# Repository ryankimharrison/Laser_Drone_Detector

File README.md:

# Laser Turret

An experimental two-camera pan/tilt tracking platform that detects a handheld DGI drone, follows it with a differential stepper mechanism, and controls a low-power green laser through a deliberately fail-closed software interlock.

The narrow C270 has been replaced with an OV9281-class camera (exact USB module
still to be commissioned). See [CAMERA_UPGRADE.md](CAMERA_UPGRADE.md) for camera
profiles, required recalibration, the 5–10 m indoor flight dataset workflow, and
timing configuration. The replacement profile is tracking-only. Historical
measurements below describe the original rig unless explicitly stated otherwise.

This README explains both the big picture and the implementation. In plain language: a Windows computer watches two cameras, identifies the drone, estimates where it is moving, and asks a Raspberry Pi Pico to turn two motors. The laser is a separate output. Tracking the drone does **not** automatically permit the laser to turn on; a set of additional checks must all pass on every control cycle.

## What is in this repository?

| Area | Purpose |
|---|---|
| `turret_host/` | Windows/Python application: cameras, object and face detection, tracking, motion control, GUI, calibration, logging, and serial communication |
| `firmware/current/` | Current MicroPython firmware for the Raspberry Pi Pico |
| `turret-2026-03-27_134819/` | KiCad schematic and PCB layout for controller board revision `3/27/2026 prod v1` |
| `tools/` | Calibration, deployment, diagnostics, replay, registration, and analysis utilities |
| `tests/` | Host-side regression tests, principally for telemetry and microstepping |
| `dataset/`, `models/`, `weights/` | Local training data and detector artifacts; most generated content is intentionally ignored by Git |
| `firmware/backups/` | Historical, timestamped firmware snapshots; useful for archaeology, not the current implementation |
| `staged/` | Proposed patches and experiments that may not be active |

The authoritative implementation paths are `turret_host/`, `firmware/current/`, and the KiCad project. Documents such as `AGENT_HANDOFF.md`, `DETECTION_BRIEF.md`, session notes, and staged patches preserve valuable history, but some statements in them have since been superseded by measurements or code changes.

## System overview

The physical head carries a narrow camera, a wide camera, a laser, and an inertial measurement unit (IMU). Two stepper motors drive a differential wrist. The computer performs the expensive vision and tracking work; the Pico generates accurate step pulses, applies motion limits, operates switched outputs, and stops motion if host commands disappear.

```mermaid
flowchart LR
    W[Wide camera<br/>find and reacquire] --> DW[Wide detector]
    N[Narrow camera<br/>precision tracking] --> DN[Drone detector]
    N --> F[YuNet face detector]
    DW --> X[Wide-to-narrow mapping]
    DN --> T[Pixel tracker]
    X --> T
    T --> C[Controller]
    F --> I[Laser interlock]
    C --> I
    I --> L[Serial link]
    L --> P[Raspberry Pi Pico]
    P --> M[Two stepper drivers]
    P --> Q[Laser MOSFET]
    IMU[Payload IMU] --> P
    P --> L
```

The design separates responsibilities:

- The **host computer** understands images, chooses a target, predicts motion, calculates motor rates, presents status, and decides whether the laser is permitted.
- The **Pico firmware** performs deterministic pulse generation, differential kinematics, acceleration limiting, travel guarding, output control, and a 400 ms command watchdog.
- The **PCB** connects power, the Pico, plug-in stepper drivers, motor and sensor headers, and three MOSFET-switched loads.

## How one frame becomes motion

1. Dedicated capture threads continuously grab the newest narrow and wide camera frames.
2. YOLO detects candidate drones. Wide-camera detections can help find a target outside the narrow field of view.
3. A stateful pixel tracker associates detections across frames and estimates position and velocity.
4. The controller compares the predicted target position with the calibrated laser aim point.
5. A measured image Jacobian converts the required image motion into signed rates for the two motors.
6. The host sends `vel <motor-a> <motor-b>` commands over USB serial.
7. The Pico ramps toward those rates and generates step pulses using RP2040 PIO hardware.
8. If new commands stop arriving for 400 ms, the firmware ramps the motors to zero and cuts the laser.

Instead of queues, threads exchange data through a `Slot`: a one-item, newest-wins mailbox. This is important for real-time behavior. If vision falls behind, processing an old queue of frames would make the turret chase where the target *was*. A slot lets a slow consumer skip frames and act on the freshest available observation.

## Computer vision and target tracking

### Two cameras, two roles

The **wide camera** provides situational awareness and reacquisition. It is an SVPRO USBFHD01M/OV2710 module with an approximately 108° horizontal field of view. It normally runs at 1920×1080 at 30 fps, with an optional 1280×720 at 60 fps mode.

The **narrow camera** provides the precision image coordinate system. Its replacement profile is provisionally 1280×800 at 30 fps, monochrome and global shutter; USB identity, lens, mode, exposure and mounting must be commissioned. The previous C270 ran at 1280×720 at 30 fps, mounted 90° clockwise with its IR-cut filter removed, and remains available as an explicit comparison profile. Camera-dependent calibration is checked against the selected camera, lens, size and mount.

The wide-to-narrow transformation can steer the turret toward a target seen only by the wide camera. It includes camera rotation, focal-length scaling, and optional fitted registration. However, parallax and calibration error mean a wide-origin box is never considered precise enough to authorize the laser. The design rule is:

> **Track on either camera; fire only from current narrow-camera evidence.**

### Drone detection

`turret_host/detector.py` wraps an Ultralytics YOLO detector. The active default is the project-specific `drone_y11n_v4_1280.pt`, run at 1280-pixel input size with FP16 enabled where supported. Only the `drone` class is selected.

The detector proposes boxes; it does not by itself decide which box to follow or whether the laser may operate. Training and capture utilities support collecting in-domain images, pre-labeling them, reviewing labels, and training a small model. This matters because the real scene—a close drone held in a hand, indoors, with partial occlusion and altered camera color response—is unlike the small outdoor drones found in most public datasets.

### Association and prediction

`turret_host/tracker.py` implements a pixel-space Kalman tracker with state:

```text
[horizontal position, vertical position, horizontal velocity, vertical velocity]
```

It uses confidence, spatial gating, box geometry, and continuity to associate detections. Adaptive process noise lets it remain smooth during steady motion while responding more quickly when the target changes direction. Its state machine is:

- `SEARCH`: no reliable target.
- `ACQUIRE`: a candidate is being confirmed.
- `TRACK`: the detector and filter agree on a target.
- `COAST`: detections were briefly lost, so the filter is predicting without fresh pixel evidence.

Coasting is useful for smooth pointing but is **not** sufficient permission to fire. The interlock requires a fresh narrow-camera drone box, not just a plausible prediction.

Range is estimated from apparent drone size when possible and may be supplemented by camera geometry. The assumed physical drone width is part of the configuration, so this is an estimate rather than a depth sensor measurement.

### Motion compensation and control

The controller combines two ideas:

- **Proportional correction** moves the target toward the goal pixel.
- **Feedforward** uses estimated target velocity so the turret moves with the target instead of always lagging behind it.

The core control law is conceptually:

```text
motor rate = - inverse(image Jacobian) × (position correction + target image velocity)
```

The image Jacobian is measured during calibration by moving the mechanism and observing how a stationary scene shifts in the camera. Its sign and scale are machine-specific. Rates are clamped, derated near travel limits, and converted through the differential mechanism. Optical flow and IMU-derived platform motion can improve the velocity estimate; their quality gates and fallbacks are logged so recorded runs can be analyzed rather than tuned by impression.

## How face protection works

The active face detector is OpenCV YuNet. It runs in a dedicated thread on the **narrow camera** because CPU inference can take longer than one camera frame period. YuNet expects upright faces, so the narrow image is rotated to compensate for the camera's 90° physical mounting. Detected boxes are then mapped back to the raw narrow-camera coordinate system used by tracking and control.

The interlock measures the distance between every detected face box and the intended beam path. The path is treated as a segment between the calibrated laser goal and current target location rather than as a single point. If a face is within the configured 120-pixel exclusion margin, the laser is inhibited.

Just as importantly, a missing or old face report is treated as **unknown**, not “no face.” A stalled detector, dead camera thread, clock error, or face result older than 200 ms therefore turns the laser off.

### The laser permission checklist

`LaserInterlock` grants permission only when **all** of the following are true:

| Check | Meaning |
|---|---|
| Armed | Both configuration and the operator's deliberate arm action allow laser use |
| Tracking | The tracker is in confirmed `TRACK`, not searching, acquiring, or coasting |
| Goal calibrated | The image location where the beam lands has been physically measured |
| Fresh drone lock | A recent narrow-camera drone box exists and contains the entire beam path |
| Plausible shape | The box aspect ratio is consistent with the measured drone, rejecting a known hand-like false positive |
| Fresh face report | The face detector has reported recently enough to be trusted |
| Face clear | Every face is farther than the inhibit margin from the beam path |
| Settled | The platform angular rate is below the firing threshold |
| Aim error small | The tracked target is close enough to the calibrated beam point |
| Velocity stream fresh | A motion command was successfully sent within the last 100 ms |
| Duty limit | Continuous on-time has not exceeded the configured cap; a cooldown follows a trip |

The logic is permission-based: a current drone detection under the beam is positive evidence. Merely failing to see a face is never enough. On any failed check, the desired laser state changes to off before normal motion work continues.

Additional protections include:

- Operator stop, disarm, E-stop, shutdown, and dead-worker events set a host-side **latched safety veto**. It can only be cleared by a new human arm action.
- Arming on real hardware invokes a live face-interlock verification procedure.
- A refused firmware `laser on` is not retried forever.
- The serial writer prioritizes laser state transitions and reports when a dead link makes software unable to confirm that the beam is off.
- Firmware boot and exception paths park STEP/DIR and all MOSFET gates low.
- The velocity watchdog cuts the laser as well as stopping motion.

### What this protection cannot guarantee

The software currently detects **visible faces**, not all human heads. YuNet can miss profiles, the back of a head, heavy occlusion, poor lighting, motion blur, or a strongly tilted face. The repository records a known loss around 35° of in-plane head tilt in one test configuration. The 200 ms allowable report age also permits real-world motion within the safety margin.

Only narrow-camera faces participate in the firing veto. Wide-camera face boxes are drawn for awareness but are not geometrically calibrated into the beam coordinate system and do not gate the laser.

No software command can switch off a laser after power or serial control has failed in a state that leaves the output energized. A physical, normally-off power interlock, keyed enable, emergency stop that removes laser power, enclosure/beam stop, and appropriate protective eyewear are outside this repository and remain necessary. Cheap 532 nm DPSS modules may also emit invisible infrared unless properly filtered.

## Firmware architecture

The firmware runs on a Raspberry Pi Pico/RP2040 under MicroPython.

| Module | Responsibility |
|---|---|
| `main.py` | Safe boot, pin parking, and console startup |
| `cli.py` | USB serial command protocol and operational workflows |
| `stepper.py` | PIO step generation, position moves, velocity loop, acceleration, watchdog, and optional microstep profiles |
| `kinematics.py` | Differential transform between motor motion and payload pitch/yaw |
| `guard.py` | IMU-backed crash/travel protection |
| `imu.py` | GY-85 gyro, accelerometer, and magnetometer drivers |
| `datum.py` | Gravity/yaw datum handling |
| `endstop.py` | Endstop debouncing, homing, and repeatability tests |
| `peripherals.py` | Laser, IR light, fan, ultrasonic, analog, and I²C devices with safety checks |
| `pinmap.py` | Copper-verified board wiring; the hardware source of truth |
| `config.py` | Driver type, mechanics, limits, interlocks, and timing |
| `diagnostics.py` | Electrical and motion self-tests |

The differential wrist is not a conventional independent pan motor plus tilt motor. Both motors moving in the same direction produce pitch; moving oppositely produces yaw. Each motor by itself produces a mixture. `kinematics.py` performs this transform using the 26-tooth motor and 60-tooth miter pulley ratio.

Position moves and continuous velocity mode use RP2040 PIO state machines for deterministic pulses. A 5 ms firmware velocity tick ramps rates and enforces limits. Dynamic microstepping exists but is disabled by default because measured switching disturbances outweighed its benefit on this drivetrain.

## PCB and hardware design

The KiCad design is a single controller/carrier board centered on:

- **A1 — Raspberry Pi Pico:** USB-connected control computer and I/O controller.
- **A2/A3 — Pololu-format stepper sockets:** intended symbol is DRV8825, while the installed/configured drivers are A4988-compatible modules.
- **U1 — XL1509-5.0 buck regulator:** creates the board's 5 V rail from the external motor supply, with L1, D1, and bulk capacitors.
- **Q1/Q2/Q4 — low-side N-channel MOSFET outputs:** switch the laser, IR illuminator, and fan.
- **J2/J3:** four-wire motor coil connectors.
- **J13/J14:** endstop connectors.
- **J5/J11:** sensor/I²C connections; the GY-85 is configured on J5/I²C0.
- **J10/J9/J7:** laser, IR, and fan switched-load connectors.

The Pico is USB-powered; the PCB's 5 V rail does not feed Pico `VSYS`. Grounds are common. This means the controller does not operate as a standalone board without USB power.

### GPIO summary

| Function | GPIO |
|---|---:|
| Tilt motor DIR / STEP | 0 / 1 |
| Tilt microstep M2/M1/M0 / enable | 2 / 3 / 4 / 5 |
| Tilt driver pad 2 | 6 |
| Pan motor DIR / STEP | 7 / 8 |
| Pan microstep M2/M1/M0 / enable | 9 / 10 / 11 / 12 |
| Pan driver pad 2 | 13 |
| IR / fan / endstop 1 / laser | 14 / 15 / 16 / 17 |
| Endstop 2 | 19 |
| J5 I²C0 SDA/SCL | 20 / 21 |
| J11 I²C1 SDA/SCL | 26 / 27 |
| Analog input | 28 / ADC2 |

### Important PCB findings and rework

These are facts encoded in `firmware/current/pinmap.py` and `config.py`, not generic warnings:

1. **Tilt STEP and DIR net labels are swapped in the schematic.** The copper is usable; firmware follows the physically verified GPIO0=DIR and GPIO1=STEP mapping.
2. **Driver socket pad 2 differs between DRV8825 and A4988.** It is `FAULT` on a DRV8825 but logic `VDD` on an A4988. The current configuration drives it from a Pico GPIO as an acknowledged, marginal workaround; the documented preferred rework is a proper 3.3 V connection.
3. **RESET/SLEEP is reportedly tied to 5 V.** This violates the A4988 input limit when its logic supply is 3.3 V and is explicitly recorded as an accepted out-of-spec condition, not a safe design recommendation.
4. **Several sensor connectors expose 5 V next to direct RP2040 inputs.** The ultrasonic echo, analog sensor return, and powered endstop arrangements have no divider or clamp. RP2040 GPIO is not 5 V tolerant; only dry-contact-to-ground endstops or verified 3.3 V signals are safe.
5. **The motor connectors are mirrored.** Each keeps a coil on adjacent pins, but supplied interleaved looms must be re-pinned so each coil occupies pins 1–2 or 3–4. Incorrect wiring can make a motor buzz and overheat its driver.
6. **The TO-220 MOSFET footprint pin order did not match a standard device.** Q1/Q2/Q4 require crossed gate/drain leads or a matching pinout. Current config says this rework was completed; verify the physical board.
7. **There are no on-board I²C pull-ups.** Any attached module must provide correctly referenced 3.3 V pull-ups.

For any new revision, these should be corrected in copper instead of perpetuated as assembly workarounds.

## Homing, calibration, and coordinate systems

The turret has multiple coordinate systems: wide pixels, raw narrow pixels, upright display pixels, motor microsteps, payload pitch/yaw, and the real laser spot. Calibration is what connects them.

At startup, the normal application establishes a repeatable datum by checking the link, calibrating gyro bias, leveling from gravity, finding a yaw reference, applying a consistent backlash preload, and setting home. Pitch is observable from gravity. Yaw is not; the project uses the repeatable magnetic field of the nearby motors as a local datum rather than trusting it as a compass.

Required calibration artifacts include:

- **Image Jacobian:** how motor steps move a stationary feature in the narrow image.
- **Goal pixel:** where the real laser spot lands in the narrow image. Frame center is acceptable for aiming experiments but never for firing permission.
- **Wide-to-narrow registration:** how a wide detection maps into the narrow camera for reacquisition.
- **Camera/latency measurements:** focal geometry, exposure, frame delivery, and end-to-end delay.

Mechanical backlash was measured around 0.57°, so homing approaches the final datum from a consistent direction.

## Running the software

The recorded development environment is Windows with Python 3.12, OpenCV, NumPy, Pillow, pyserial, PyTorch with CUDA, and Ultralytics. A `.venv` directory exists in this checkout, but virtual environments are machine-specific and its Python launcher may point to an interpreter that is no longer installed. The repository currently has no reproducible lock file; treat the environment description as informative rather than a clean-install guarantee, and rebuild the environment locally when necessary.

Start safely with simulation and no GUI:

```powershell
.\.venv\Scripts\python.exe -m turret_host.app --no-hardware --no-gui --run-seconds 5
```

Run simulation with the spectator GUI:

```powershell
.\.venv\Scripts\python.exe -m turret_host.app --no-hardware
```

Run with real cameras and motion but force tracking-only behavior:

```powershell
.\.venv\Scripts\python.exe -m turret_host.app --tracking-only
```

The real-hardware default performs homing and may move the mechanism. Keep the laser power physically disconnected during commissioning. Useful options include `--port`, `--cpu`, `--wide-fast`, `--fast-home`, `--skip-level`, `--record DIR`, and `--run-seconds N`; use `--help` for the current list.

## Verification and diagnostics

Tests that do not require attached hardware:

```powershell
.\.venv\Scripts\python.exe -m compileall -q turret_host
.\.venv\Scripts\python.exe -m unittest discover -s tests
.\.venv\Scripts\python.exe -m turret_host.control
.\.venv\Scripts\python.exe -m turret_host.tracker
```

Many utilities in `tools/` intentionally talk to real hardware or cameras. Read their arguments and source before running them. In particular, deployment, homing, calibration, step, lash, and structured-light tools can cause motion or light emission.

The application can record synchronized telemetry for after-action analysis. The supporting scripts study latency, clock alignment, step integrity, image registration, optical-flow velocity, aim residuals, and mechanical skew. This measurement-first approach is central to the project: motor counts alone cannot reveal a skipped belt or stalled mechanism, and a visually smooth demo does not prove that the safety gates worked.

## Known limitations and current status

- This working tree is an active prototype with uncommitted current-code changes and staged experiments.
- Laser enable is currently `True` in both `turret_host/config.py` and `firmware/current/config.py`. The GUI still requires deliberate arming and the interlock still applies, but configuration is not a physical safety barrier.
- Face detection is a safety aid with known blind spots, not proof that no head is present.
- Wide-camera detections can steer but cannot authorize firing.
- Several camera intrinsics and offsets began as estimates; verify which calibration JSON artifacts exist on the actual machine.
- Dead reckoning can diverge when motors skip. The payload accelerometer independently measures tilt, but it cannot directly observe yaw near level.
- The software soft limits do not replace mechanical stops. The payload is documented as ±90° pitch with a ±225° yaw wiring limit.
- The host presently caps normal motor commands at 1000 microsteps/s pending further delivery testing, below firmware's higher electrical ceiling.
- Hardware notes describe accepted out-of-spec wiring. A production revision should add real level shifting/protection and a hardware laser-interlock chain.

## Design principles worth preserving

- **Fail closed:** uncertainty removes permission; it never creates it.
- **Freshness is data:** every frame, face report, detection, and command carries time information.
- **Newest wins:** discard stale work instead of building a real-time backlog.
- **Measure geometry:** do not hide sign errors or physical offsets in tuning constants.
- **Separate tracking from firing:** a prediction may steer, but only current narrow-camera evidence can permit light.
- **Independent witnesses:** use camera evidence, serial freshness, IMU attitude, firmware watchdogs, and human controls for different failure modes.
- **Preserve provenance:** a mapped wide-camera box remembers that it came from the wide camera and can never accidentally become firing evidence.

## Further reading

- `turret_host/BUILD_SPEC.md` — host design contract and hard-won implementation constraints.
- `turret_host/STATUS.md` — an older formal safety review; useful history, but some configuration values are now outdated.
- `AGENT_HANDOFF.md` — detailed hardware measurements, firmware protocol, and project history.
- `DETECTION_BRIEF.md` — rationale for the custom drone dataset and detector training approach.
- `PLAN_NEXT_STAGE.md` and session notes — experimental results and next-stage control analysis.
- `firmware/current/pinmap.py` — the copper-verified wiring source of truth.

## Responsible use

This project combines automated aiming, moving machinery, exposed electronics, and laser emission. Operate it only in a controlled indoor test area with a beam stop, exclusion zone, direct supervision, and a physical means to remove laser power. Begin with the laser disconnected and substitute a harmless indicator during software development. Compliance with local laser, electrical, workplace, and aviation rules is the operator's responsibility.

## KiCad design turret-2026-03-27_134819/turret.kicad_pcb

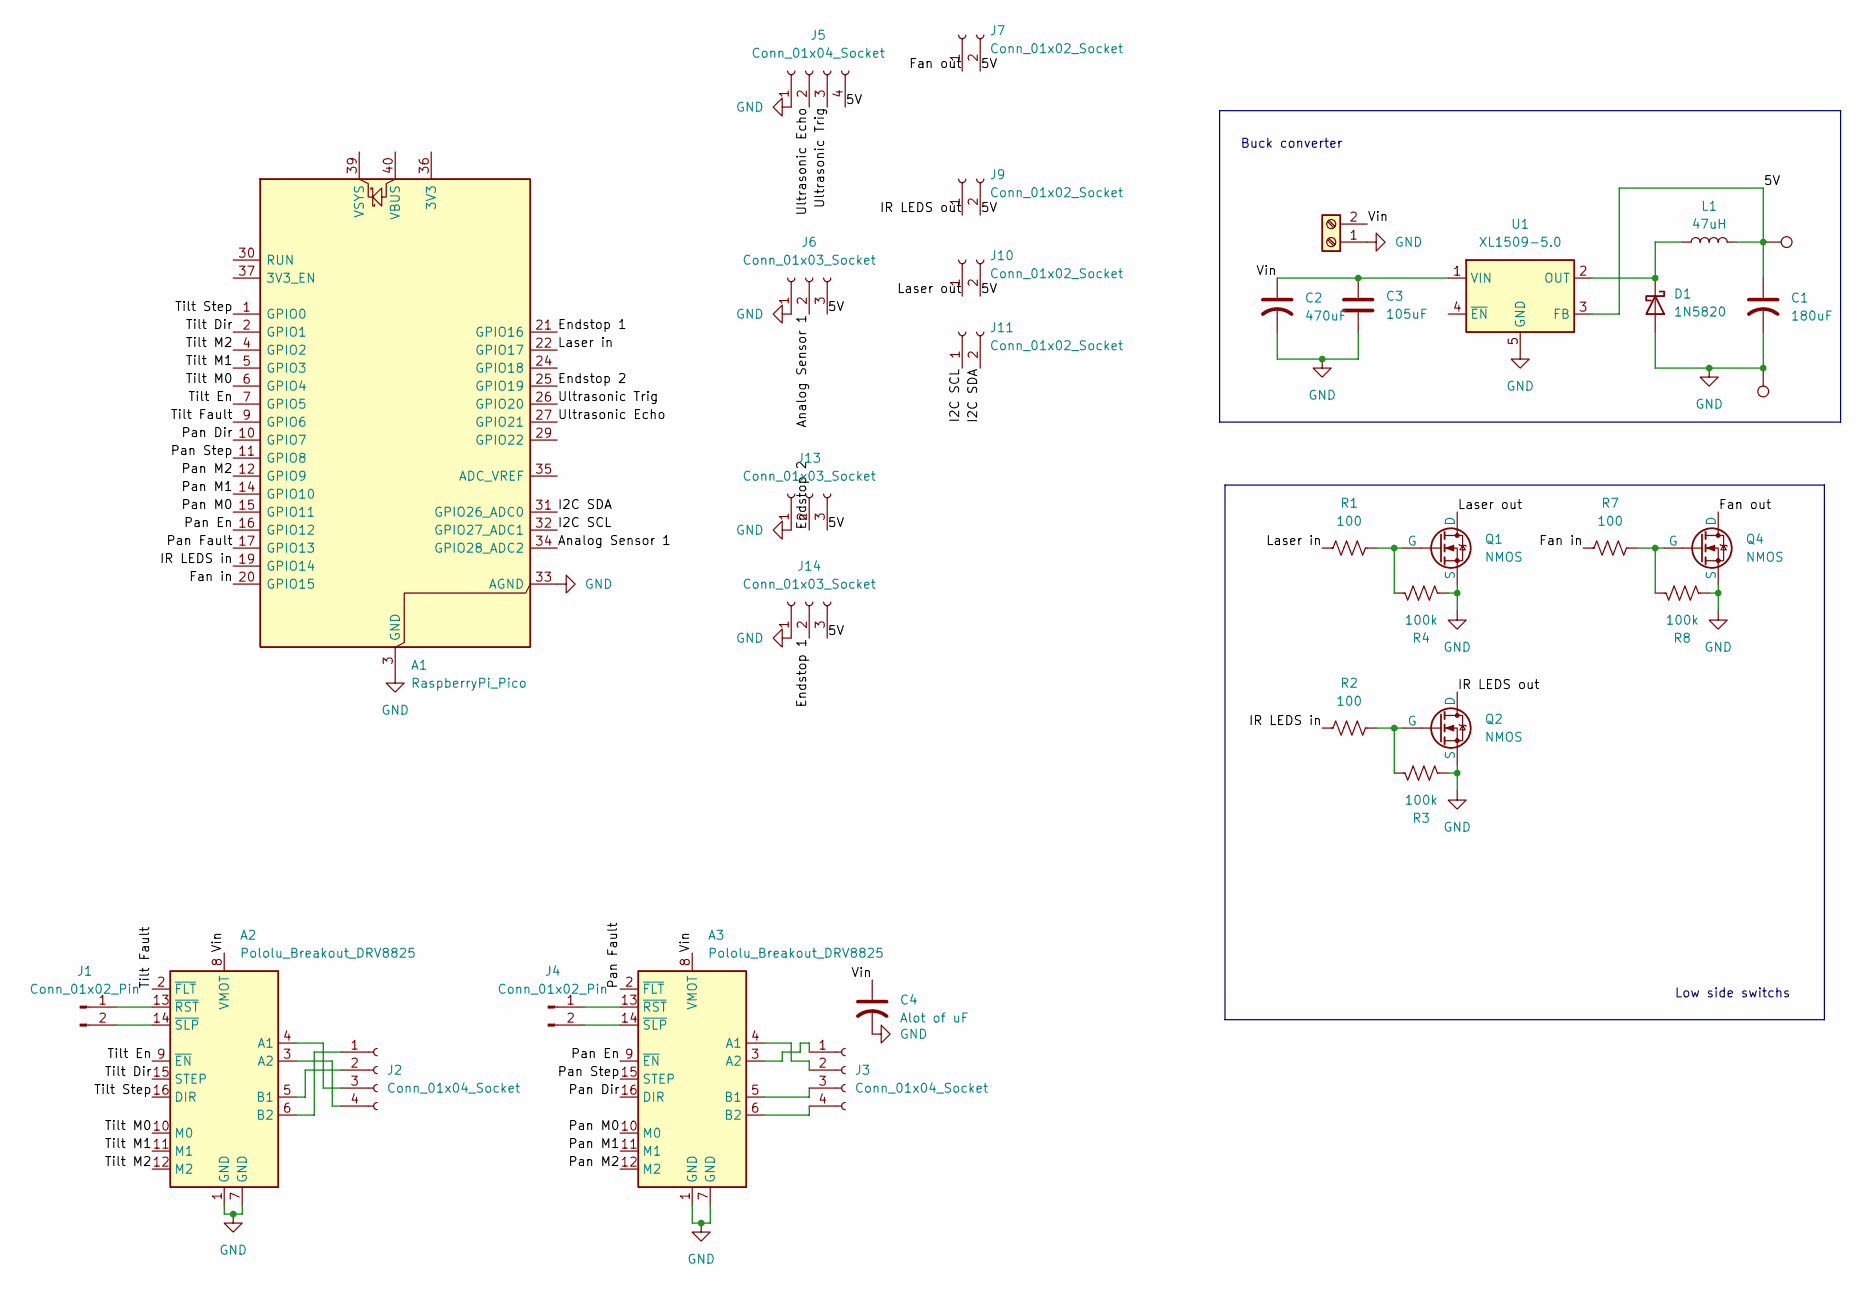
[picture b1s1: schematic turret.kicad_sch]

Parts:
A1: RaspberryPi_Pico; RaspberryPi_Pico_Common_Unspecified
A2, A3: Pololu_Breakout_DRV8825; Pololu_Breakout-16_15.2x20.3mm
C1: 180uF; C_Radial_D8.0mm_H11.5mm_P3.50mm
C2: 470uF; C_Radial_D8.0mm_H11.5mm_P3.50mm
C3: 105uF; C_Radial_D8.0mm_H11.5mm_P3.50mm
C4: Alot of uF; C_Radial_D16.0mm_H25.0mm_P7.50mm
D1: 1N5820; D_DO-201AD_P15.24mm_Horizontal
J1, J4: Conn_01x02_Pin; PinSocket_1x02_P2.54mm_Vertical
J2, J3, J5: Conn_01x04_Socket; JST_XH_B4B-XH-A_1x04_P2.50mm_Vertical
J6, J13, J14: Conn_01x03_Socket; JST_XH_B3B-XH-A_1x03_P2.50mm_Vertical
J7, J9, J10, J11: Conn_01x02_Socket; JST_XH_B2B-XH-A_1x02_P2.50mm_Vertical
J12: Screw_Terminal_01x02; TerminalBlock_Phoenix_MKDS-3-2-5.08_1x02_P5.08mm_Horizontal
L1: 47uH; L_10.4x10.4_H4.8
Q1, Q2, Q4: NMOS; TO-220-3_Vertical
R1, R2, R7: 100; R_Axial_DIN0207_L6.3mm_D2.5mm_P10.16mm_Horizontal
R3, R4, R8: 100k; R_Axial_DIN0207_L6.3mm_D2.5mm_P10.16mm_Horizontal
TP14, TP17: TestPoint; TestPoint_Pad_D3.0mm
U1: XL1509-5.0; SOIC-8_3.9x4.9mm_P1.27mm

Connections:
/5V: C1.1, J5.4, J6.3, J7.2, J9.2, J10.2, J13.3, J14.3, L1.2, TP14.1, U1.3 (FB)
/Analog Sensor 1: A1.34 (GPIO28_ADC2), J6.2
/Endstop 1: A1.21 (GPIO16), J14.2
/Endstop 2: A1.25 (GPIO19), J13.2
/Fan in: A1.20 (GPIO15), R7.1
/Fan out: J7.1, Q4.1 (D)
/I2C SCL: A1.32 (GPIO27_ADC1), J11.1
/I2C SDA: A1.31 (GPIO26_ADC0), J11.2
/IR LEDS in: A1.19 (GPIO14), R2.1
/IR LEDS out: J9.1, Q2.1 (D)
/Laser in: A1.22 (GPIO17), R1.1
/Laser out: J10.1, Q1.1 (D)
/Pan Dir: A1.10 (GPIO7), A3.16 (DIR)
/Pan En: A1.16 (GPIO12), A3.9 (~EN)
/Pan Fault: A1.17 (GPIO13), A3.2 (~FLT)
/Pan M0: A1.15 (GPIO11), A3.10 (M0)
/Pan M1: A1.14 (GPIO10), A3.11 (M1)
/Pan M2: A1.12 (GPIO9), A3.12 (M2)
/Pan Step: A1.11 (GPIO8), A3.15 (STEP)
/Tilt Dir: A1.2 (GPIO1), A2.15 (STEP)
/Tilt En: A1.7 (GPIO5), A2.9 (~EN)
/Tilt Fault: A1.9 (GPIO6), A2.2 (~FLT)
/Tilt M0: A1.6 (GPIO4), A2.10 (M0)
/Tilt M1: A1.5 (GPIO3), A2.11 (M1)
/Tilt M2: A1.4 (GPIO2), A2.12 (M2)
/Tilt Step: A1.1 (GPIO0), A2.16 (DIR)
/Ultrasonic Echo: A1.27 (GPIO21), J5.2
/Ultrasonic Trig: A1.26 (GPIO20), J5.3
/Vin: A2.8 (VMOT), A3.8 (VMOT), C2.1, C3.1, C4.1, J12.2, U1.1 (VIN)
GND: A1.3 (GND), A1.8 (GND), A1.13 (GND), A1.18 (GND), A1.23 (GND), A1.28 (GND), A1.33 (AGND), A1.38 (GND), A2.1 (GND), A2.7 (GND), A3.1 (GND), A3.7 (GND), C1.2, C2.2, C3.2, C4.2, D1.2 (A), J5.1, J6.1, J12.1, J13.1, J14.1, Q1.3 (S), Q2.3 (S), Q4.3 (S), R3.1, R4.2, R8.1, TP17.1, U1.5 (GND), U1.6 (GND), U1.7 (GND), U1.8 (GND)
unnamed: A2.4 (A1), J2.3
unnamed: A2.3 (A2), J2.4
unnamed: A2.5 (B1), J2.2
unnamed: A2.6 (B2), J2.1
unnamed: A2.13 (~RST), J1.1
unnamed: A2.14 (~SLP), J1.2
unnamed: A3.4 (A1), J3.2
unnamed: A3.3 (A2), J3.1
unnamed: A3.5 (B1), J3.3
unnamed: A3.6 (B2), J3.4
unnamed: A3.13 (~RST), J4.1
unnamed: A3.14 (~SLP), J4.2
unnamed: D1.1 (K), L1.1, U1.2 (OUT)
unnamed: Q1.2 (G), R1.2, R4.1
unnamed: Q2.2 (G), R2.2, R3.2
unnamed: Q4.2 (G), R7.2, R8.2

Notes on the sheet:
Low side switchs
Buck converter

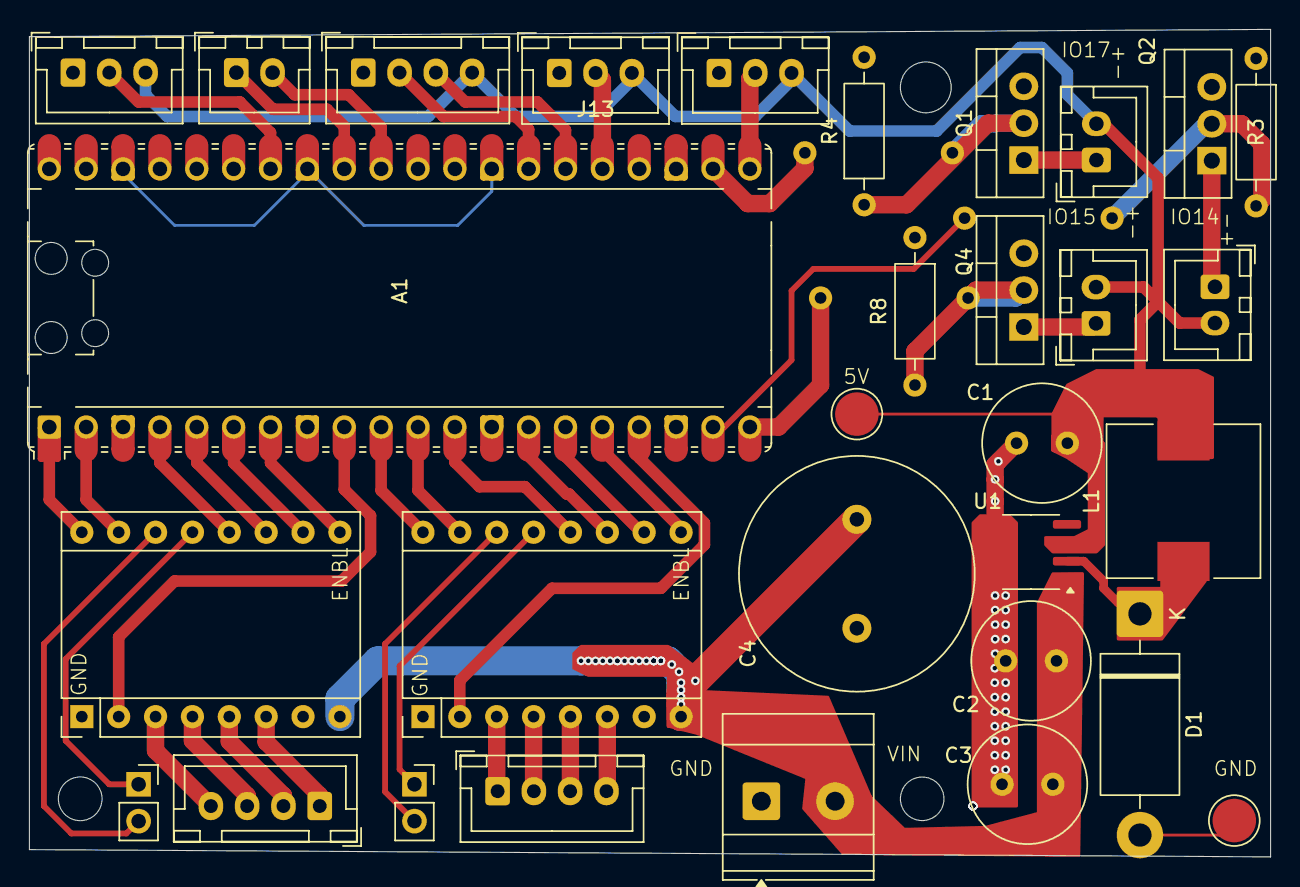
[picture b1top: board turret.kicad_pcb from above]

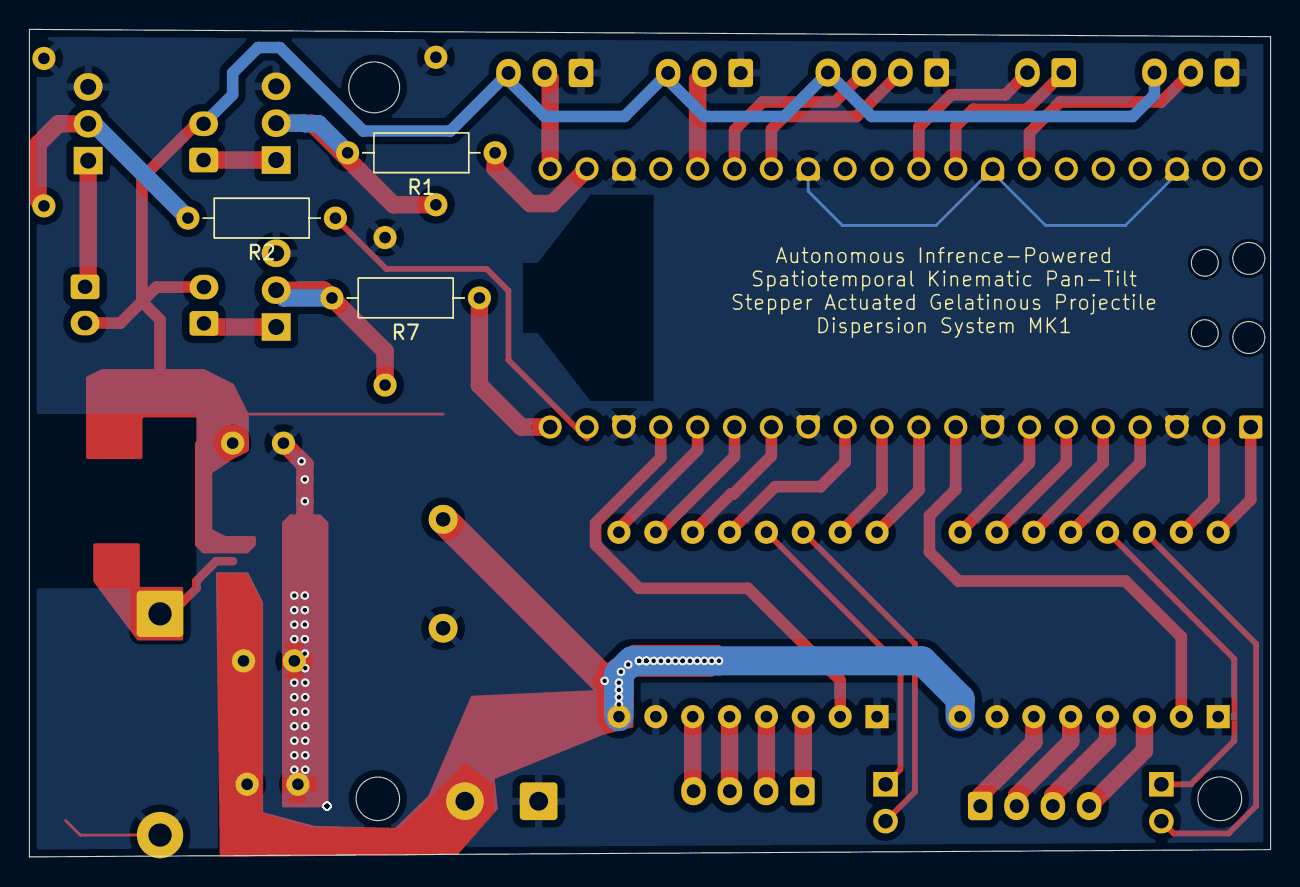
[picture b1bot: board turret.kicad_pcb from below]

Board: 2 copper layers, 85.5 x 57.0 mm, 34 parts (3 on the bottom side), 46 nets.

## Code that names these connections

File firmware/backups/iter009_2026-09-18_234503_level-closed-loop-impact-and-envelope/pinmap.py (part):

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# driver's DIR input.  The net named "/Tilt Dir" lands on A2 pad 15, which
# is the driver's STEP input.  Verified on the copper:
#
#     A2 pad 15 (STEP) <- net "/Tilt Dir"  <- Pico pad 2  = GPIO1
#     A2 pad 16 (DIR)  <- net "/Tilt Step" <- Pico pad 1  = GPIO0
#
# The BOARD IS FINE -- only the labels lie.  The values below are physical
# truth.  If you ever fix the labels in KiCad, this file does not change.
#
# The PAN axis (A3) is labelled correctly: pad 15 STEP <- GPIO8, pad 16 DIR
# <- GPIO7.  Only tilt is affected.
# --------------------------------------------------------------------------

# --------------------------------------------------------------------------
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# The ultrasonic connector doubles as a SECOND, independent I2C bus.
#
# Verified against the RP2040 datasheet, Table 2 (GPIO Bank 0 Functions):
#   GPIO20  F3 = I2C0 SDA        GPIO21  F3 = I2C0 SCL
# so J5's trig/echo pair is a genuine I2C0 bus, on a different peripheral
# instance from J11's I2C1. Both can run at the same time.
#
# WARNING -- J5 pin 4 is on the 5 V rail (Finding #3). I2C idles HIGH through
# its pull-ups, so a module whose pull-ups tie to VCC_IN rather than to its own
# regulated 3V3 will hold BOTH GPIO20 and GPIO21 at 5 V continuously. RP2040
# absolute maximum is IOVDD + 0.5 V = 3.8 V. That is not a transient overshoot,
# it is a permanent over-voltage on two pins. Measure SDA/SCL at idle before
# connecting the Pico.
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
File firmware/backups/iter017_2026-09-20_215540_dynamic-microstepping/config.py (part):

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# ==========================================================================
# Which connector the IMU is on.
#   "J11" -- the designated I2C header, I2C1 on GPIO26/27. No 5 V pin.
#   "J5"  -- the ultrasonic connector, I2C0 on GPIO20/21. Has a 5 V pin;
#            see the warning in pinmap.py before using it.
IMU_PORT = "J5"

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#   ENDSTOPS
# ==========================================================================
# Which endstop connector belongs to which axis.  None = not used.
#   J14 -> "1" (GPIO16),  J13 -> "2" (GPIO19)
ENDSTOP_AXIS = {"pan": "1", "tilt": "2"}

# Switch wiring.  The only 3.3 V-safe option is a bare mechanical switch
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
# Set True only after you have EITHER fitted a divider on the echo line OR
# swapped to a 3.3 V sensor (HC-SR04P / RCWL-1601).  A plain 5 V HC-SR04
# will slowly kill GPIO21.
ULTRASONIC_ECHO_IS_3V3_SAFE = False

# Set True only after confirming your analog sensor's output never exceeds
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VERBOSE = True

# ==========================================================================
#   FAN  (Q4, GPIO15, low-side switched -- see pinmap.OUTPUTS)
# ==========================================================================
# Run the fan whenever either axis is ENERGISED, and stop it after this long
# idle. Tied to energised rather than to velocity mode because position moves
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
